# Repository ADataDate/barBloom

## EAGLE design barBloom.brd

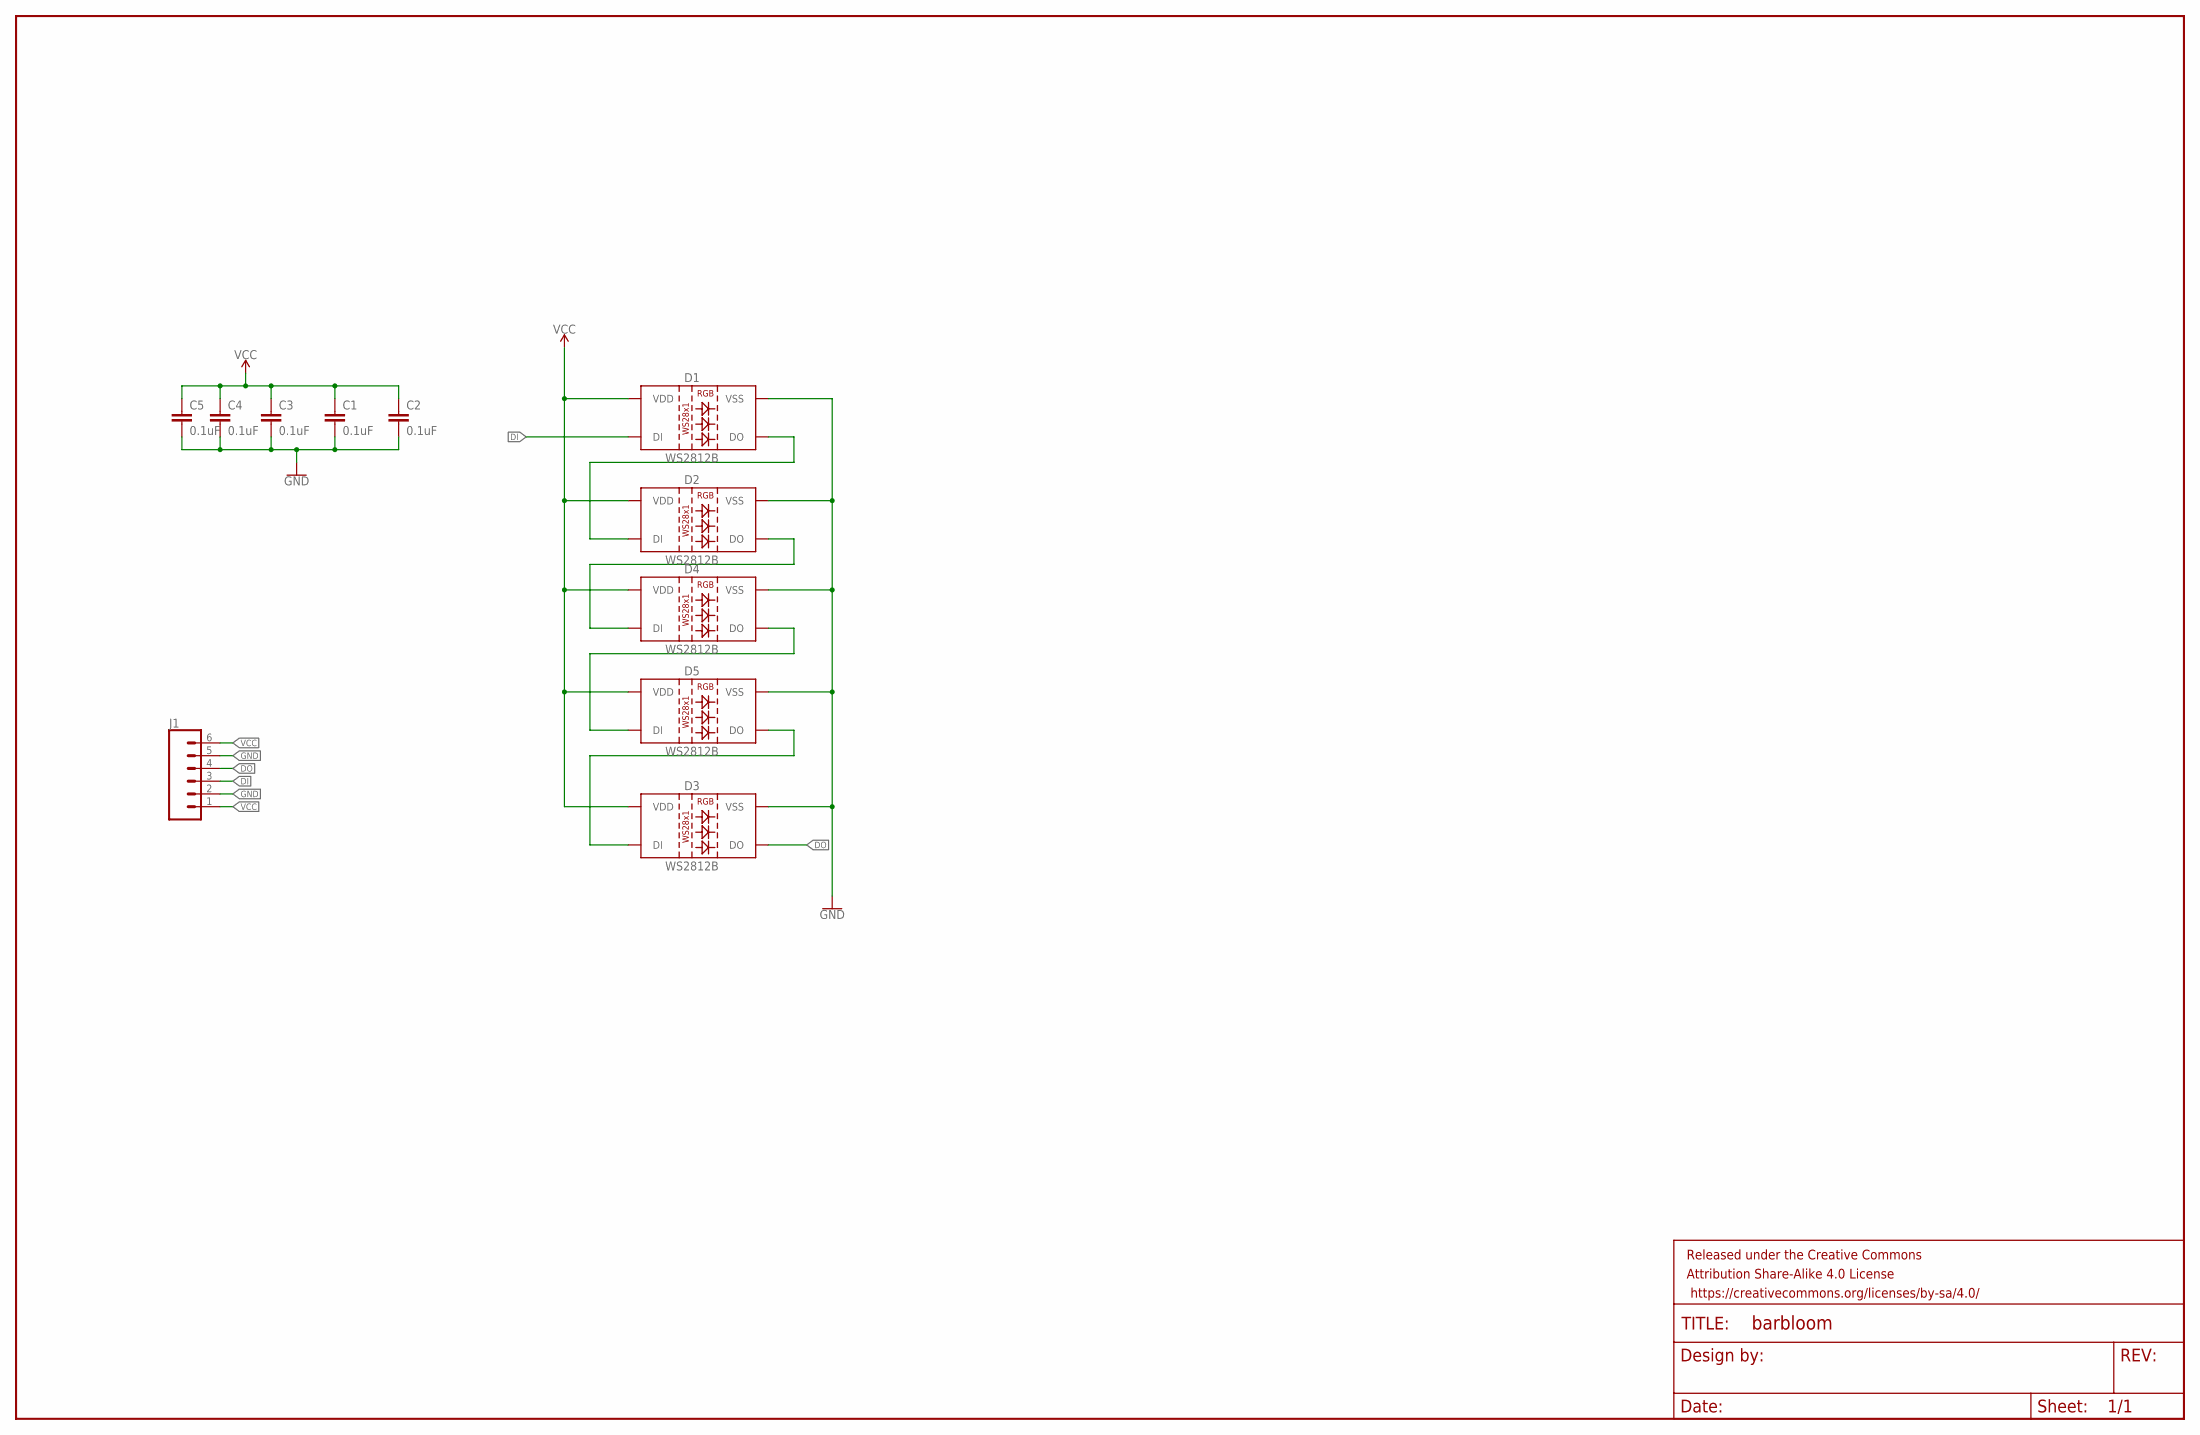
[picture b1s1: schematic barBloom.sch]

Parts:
C1, C2, C3, C4, C5: 0.1uF; 0603
D1, D2, D3, D4, D5: WS2812B
FRAME1: FRAME-LEDGER; CREATIVE_COMMONS
J1: CONN_06SMD-STRAIGHT-ALT-FEMALE; 1X06_SMD_STRAIGHT_ALT

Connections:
DI: D1.4 (DI), J1.3
DO: D3.2 (DO), J1.4
GND: C1.2, C2.2, C3.2, C4.2, C5.2, D1.3 (VSS), D2.3 (VSS), D3.3 (VSS), D4.3 (VSS), D5.3 (VSS), J1.2, J1.5
unnamed: D1.2 (DO), D2.4 (DI)
unnamed: D2.2 (DO), D4.4 (DI)
unnamed: D4.2 (DO), D5.4 (DI)
unnamed: D3.4 (DI), D5.2 (DO)
VCC: C1.1, C2.1, C3.1, C4.1, C5.1, D1.1 (VDD), D2.1 (VDD), D3.1 (VDD), D4.1 (VDD), D5.1 (VDD), J1.1, J1.6

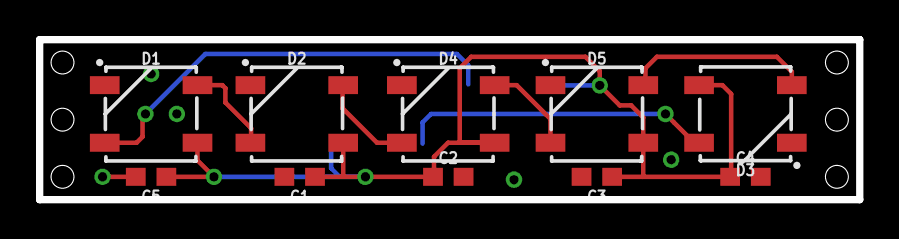
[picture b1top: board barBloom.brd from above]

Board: 2 copper layers, 45.6 x 8.9 mm, 12 parts (1 on the bottom side), 8 nets.

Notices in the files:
parts and their libraries:
SparkFun-Capacitors: Licensing: Creative Commons ShareAlike 4.0 International - https://creativecommons.org/licenses/by-sa/4.0
SparkFun-Aesthetics: Released under the Creative Commons Attribution Share-Alike 4.0 License
SparkFun-Aesthetics: https://creativecommons.org/licenses/by-sa/4.0
